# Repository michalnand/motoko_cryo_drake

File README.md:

# motoko cryo drake - line following robot

robot photos

# hardware

- main MCU stm32f722, cortex m7, 216MHz, FPU
- sensors MCU stm32g031, cortex m0, 64MHz
- BLDC motors, custom windings, custom silicone tires
- 3 phase drivers, 2 x MP6541, 8A drivers
- turbine - some random DC drone motor + 3D print
- line sensors : 10x phototransistor + white LED
- obstacle sensors : 4x IR photo diode
- power 2D LiPo, Dualsky 250mAh
- USB C, debug connectors, RGB leds

# robot PCB

4 layer pcb, designed in EasyEDA

# software 

inner loop, 2kHz : 
- FOC control for BLDC motors
- kalman filter state estimator

outer loop
- analytical MPC
- constrained path planner
- koopman operator non linear controller

# block diagram

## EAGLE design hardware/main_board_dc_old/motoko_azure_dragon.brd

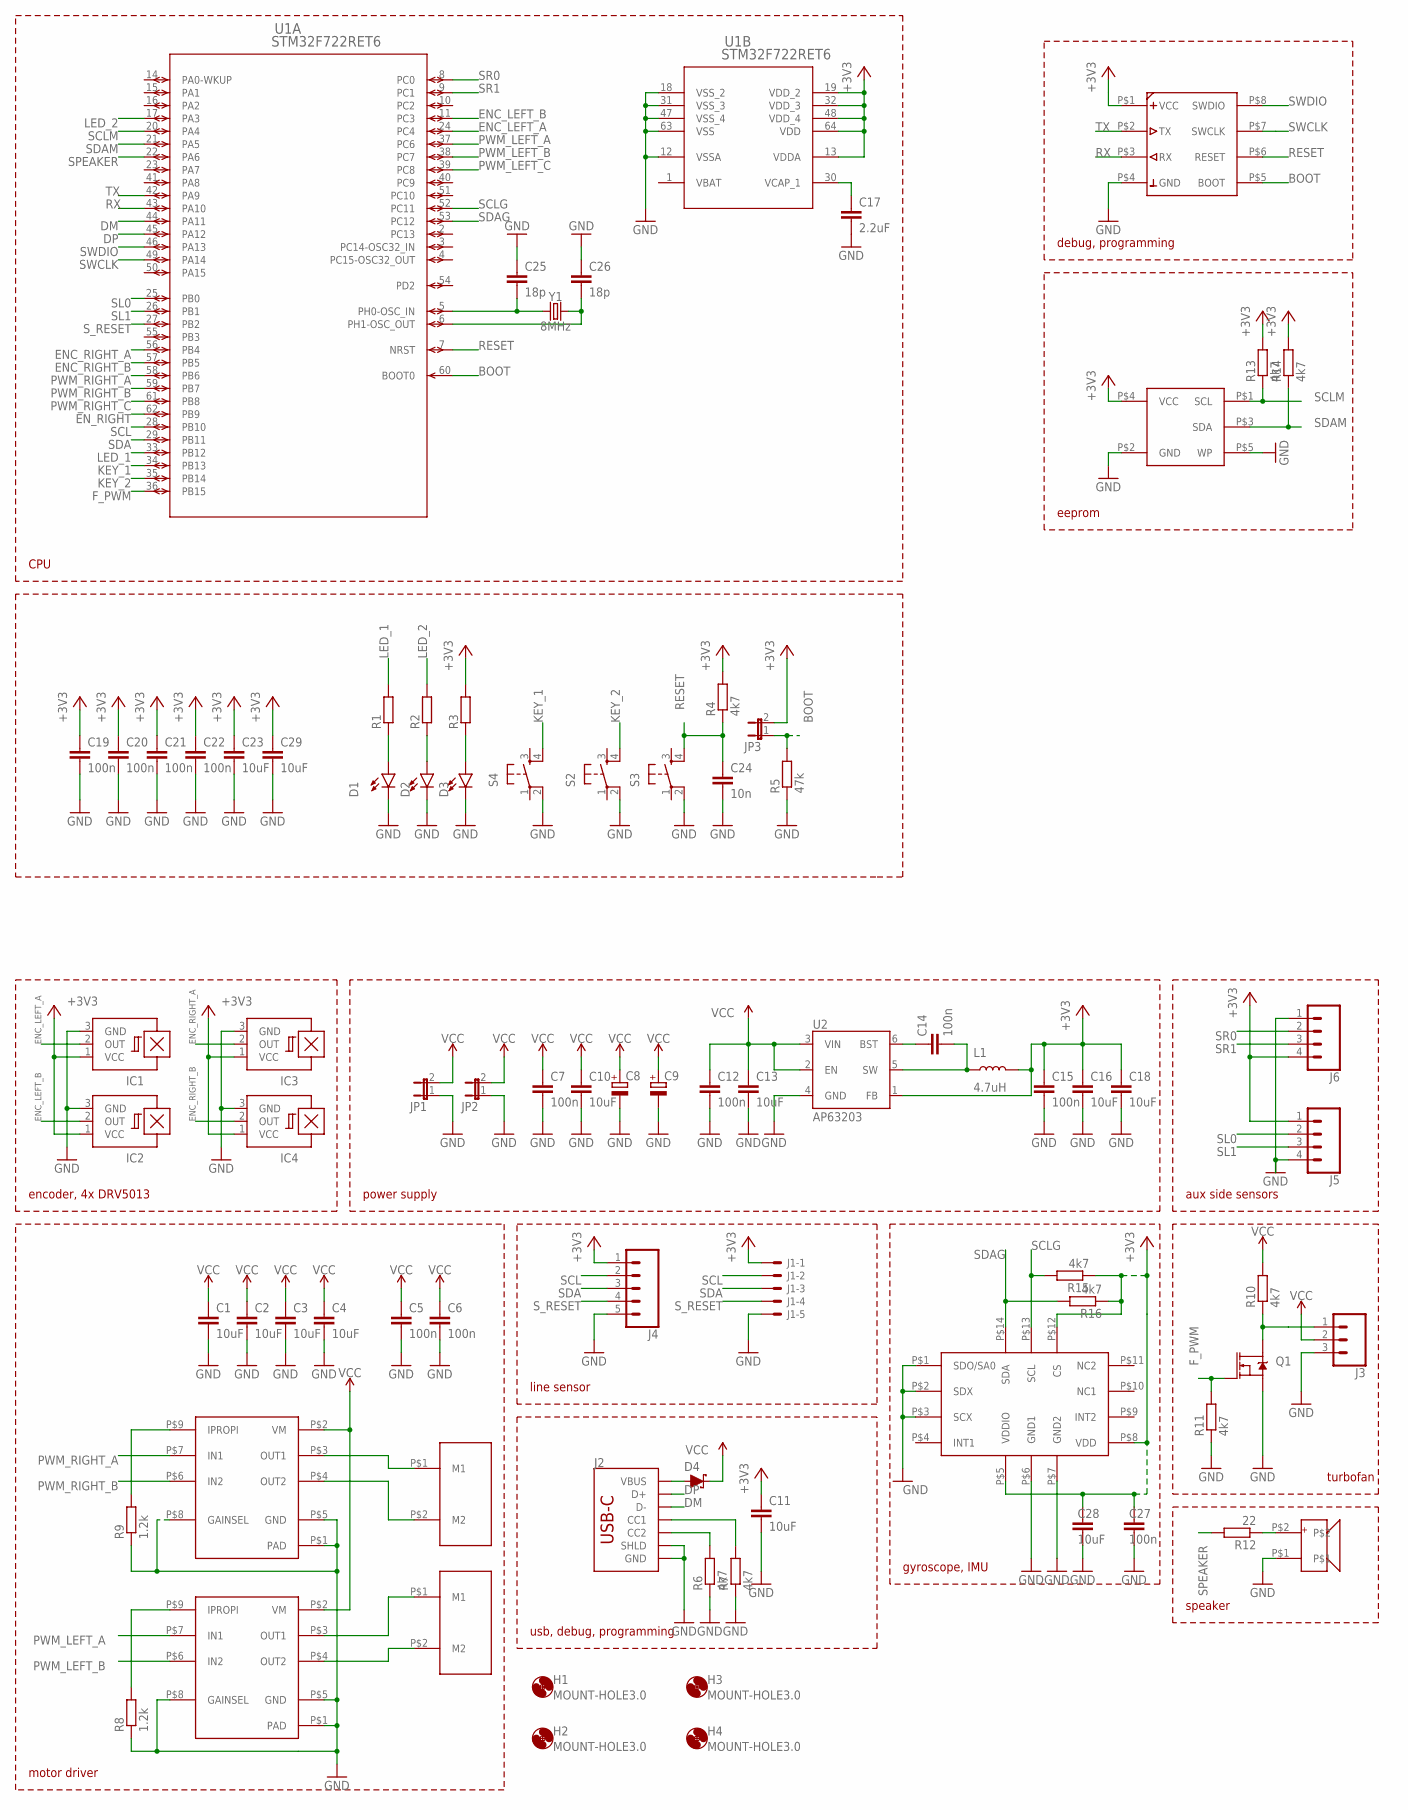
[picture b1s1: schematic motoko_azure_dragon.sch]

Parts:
C1, C2, C3, C4, C10, C11, C13, C16, C18, C23, C28, C29: 10uF; C0805
C5, C6, C7, C12, C14, C15, C19, C20, C21, C22, C27: 100n; C0805
C8, C9: CPOL-EUB/3528-21W; B/3528-21W
C17: 2.2uF; C0805
C24: 10n; C0805
C25, C26: 18p; C0805
D1, D2, D3: LED1206; LED-1206
D4: 3A/10V/280mV; SOD-323
H1, H2, H3, H4: MOUNT-HOLE3.0; 3,0
IC1, IC2, IC3, IC4: A1202LH; SOT23-W
J1: XF2L-0535-1
J2: USB_C_2-LAYER_PADS; USB-C-16P-2LAYER-PADS
J3: CONN_03LONGPADS; 1X03_LONGPADS
J4: CONN_051.27MM; 1X05_1.27MM
J5, J6: 1X04_SMD_STRAIGHT_COMBO; 1X04_SMD_VERTICAL_COMBO
JP1, JP2, JP3: JP1E; JP1
L1: 4.7uH; CR54
Q1: 5.8A/30V/35mΩ; SOT23-3
R1, R2, R3: R-EU_M0805; M0805
R4, R6, R7, R10, R11, R13, R14, R15, R16: 4k7; M0805
R5: 47k; M0805
R8, R9: 1.2k; M0805
R12: 22; M0805
S2, S3, S4: TAC_SWITCHSMD; TACTILE-SWITCH-SMD
U1: STM32F722RET6; LQFP64-10X10MM
U2: AP63203; SOT23-6
U$2, U$3: POLOLU_MICRO_METAL_GEAR_MOTOR
U$4, U$5: DRV8213; DSG8
U$6: 24LC24_SOT23; SOT23
U$7: DEBUG_CON; HEADER_4X2_1.27
U$8: LSM6DSM; LGA14L
U$9: SPEAKER_SMD_SMT0440
Y1: 8MHz; CRYSTAL-SMD-3.2X2.5MM

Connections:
+3V3: C11.1, C15.1, C16.1, C18.1, C19.1, C20.1, C21.1, C22.1, C23.1, C27.1, C28.1, C29.1, IC1.1 (VCC), IC2.1 (VCC), IC3.1 (VCC), IC4.1 (VCC), J1.1 (MSV), J4.1, J5.1, J6.4, JP3.2, L1.P$2 (2), R3.2, R4.2, R13.2, R14.2, R15.1, R16.1, U1.13 (VDDA), U1.19 (VDD_2), U1.32 (VDD_3), U1.48 (VDD_4), U1.64 (VDD), U2.1 (FB), U$6.P$4 (VCC), U$7.P$1 (VCC), U$8.P$5 (VDDIO), U$8.P$8 (VDD), U$8.P$12 (CS)
BOOT: JP3.1, R5.2, U1.60 (BOOT0), U$7.P$5 (BOOT)
DM: J2.A7 (D-), J2.B7 (D-), U1.44 (PA11)
DP: J2.A6 (D+), J2.B6 (D+), U1.45 (PA12)
ENC_LEFT_A: IC1.2 (OUT), U1.24 (PC4)
ENC_LEFT_B: IC2.2 (OUT), U1.11 (PC3)
ENC_RIGHT_A: IC3.2 (OUT), U1.56 (PB4)
ENC_RIGHT_B: IC4.2 (OUT), U1.57 (PB5)
EN_RIGHT: U1.62 (PB9)
F_PWM: Q1.1 (G), R11.2, U1.36 (PB15)
GND: C1.2, C2.2, C3.2, C4.2, C5.2, C6.2, C7.2, C8.-, C9.-, C10.2, C11.2, C12.2, C13.2, C15.2, C16.2, C17.2, C18.2, C19.2, C20.2, C21.2, C22.2, C23.2, C24.2, C25.1, C26.1, C27.2, C28.2, C29.2, D1.C, D2.C, D3.C, IC1.3 (GND), IC2.3 (GND), IC3.3 (GND), IC4.3 (GND), J1.5 (MS), J2.GND, J2.GND2 (GND), J2.SHLD1 (SHLD), J2.SHLD2 (SHLD), J2.SHLD3 (SHLD), J2.SHLD4 (SHLD), J3.3, J4.5, J5.4, J6.1, JP1.1, JP2.1, Q1.2 (S), R5.1, R6.1, R7.1, R8.1, R9.1, R11.1, S2.2, S3.2, S4.2, U1.12 (VSSA), U1.18 (VSS_2), U1.31 (VSS_3), U1.47 (VSS_4), U1.63 (VSS), U2.4 (GND), U$4.P$1 (PAD), U$4.P$5 (GND), U$4.P$8 (GAINSEL), U$5.P$1 (PAD), U$5.P$5 (GND), U$5.P$8 (GAINSEL), U$6.P$2 (GND), U$6.P$5 (WP), U$7.P$4 (GND), U$8.P$1 (SDO/SA0), U$8.P$2 (SDX), U$8.P$3 (SCX), U$8.P$6 (GND1), U$8.P$7 (GND2), U$9.P$1
KEY_1: S4.4, U1.34 (PB13)
KEY_2: S2.4, U1.35 (PB14)
LED_1: R1.2, U1.33 (PB12)
LED_2: R2.2, U1.17 (PA3)
unnamed: U$3.P$2 (M2), U$5.P$4 (OUT2)
unnamed: U$3.P$1 (M1), U$5.P$3 (OUT1)
unnamed: U$2.P$2 (M2), U$4.P$4 (OUT2)
unnamed: U$2.P$1 (M1), U$4.P$3 (OUT1)
unnamed: C14.2, L1.P$1 (1), U2.5 (SW)
unnamed: C14.1, U2.6 (BST)
unnamed: D1.A, R1.1
unnamed: D2.A, R2.1
unnamed: D3.A, R3.1
unnamed: J2.B5 (CC2), R6.2
unnamed: J2.A5 (CC1), R7.2
unnamed: C17.1, U1.30 (VCAP_1)
unnamed: C25.2, U1.5 (PH0-OSC_IN), Y1.1
unnamed: C26.2, U1.6 (PH1-OSC_OUT), Y1.3 (2)
unnamed: R8.2, U$5.P$9 (IPROPI)
unnamed: R9.2, U$4.P$9 (IPROPI)
unnamed: D4.A, J2.VBUS1 (VBUS), J2.VBUS2 (VBUS)
unnamed: J3.1, Q1.3 (D), R10.1
unnamed: R12.1, U$9.P$2
PWM_LEFT_A: U1.37 (PC6), U$5.P$7 (IN1)
PWM_LEFT_B: U1.38 (PC7), U$5.P$6 (IN2)
PWM_LEFT_C: U1.39 (PC8)
PWM_RIGHT_A: U1.58 (PB6), U$4.P$7 (IN1)
PWM_RIGHT_B: U1.59 (PB7), U$4.P$6 (IN2)
PWM_RIGHT_C: U1.61 (PB8)
RESET: C24.1, R4.1, S3.4, U1.7 (NRST), U$7.P$6 (RESET)
RX: U1.43 (PA10), U$7.P$3 (RX)
SCL: J1.2 (MS), J4.2, U1.28 (PB10)
SCLG: R15.2, U1.52 (PC11), U$8.P$13 (SCL)
SCLM: R13.1, U1.20 (PA4), U$6.P$1 (SCL)
SDA: J1.3 (MS), J4.3, U1.29 (PB11)
SDAG: R16.2, U1.53 (PC12), U$8.P$14 (SDA)
SDAM: R14.1, U1.21 (PA5), U$6.P$3 (SDA)
SL0: J5.2, U1.25 (PB0)
SL1: J5.3, U1.26 (PB1)
SPEAKER: R12.2, U1.22 (PA6)
SR0: J6.2, U1.8 (PC0)
SR1: J6.3, U1.9 (PC1)
SWCLK: U1.49 (PA14), U$7.P$7 (SWCLK)
SWDIO: U1.46 (PA13), U$7.P$8 (SWDIO)
S_RESET: J1.4 (MS), J4.4, U1.27 (PB2)
TX: U1.42 (PA9), U$7.P$2 (TX)
VBAT: U1.1 (VBAT)
VCC: C1.1, C2.1, C3.1, C4.1, C5.1, C6.1, C7.1, C8.+, C9.+, C10.1, C12.1, C13.1, D4.C, J3.2, JP1.2, JP2.2, R10.2, U2.2 (EN), U2.3 (VIN), U$4.P$2 (VM), U$5.P$2 (VM)

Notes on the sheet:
encoder, 4x DRV5013
motor driver
power supply
line sensor
aux side sensors
usb, debug, programming
turbofan
gyroscope, IMU
speaker
debug, programming
eeprom
CPU

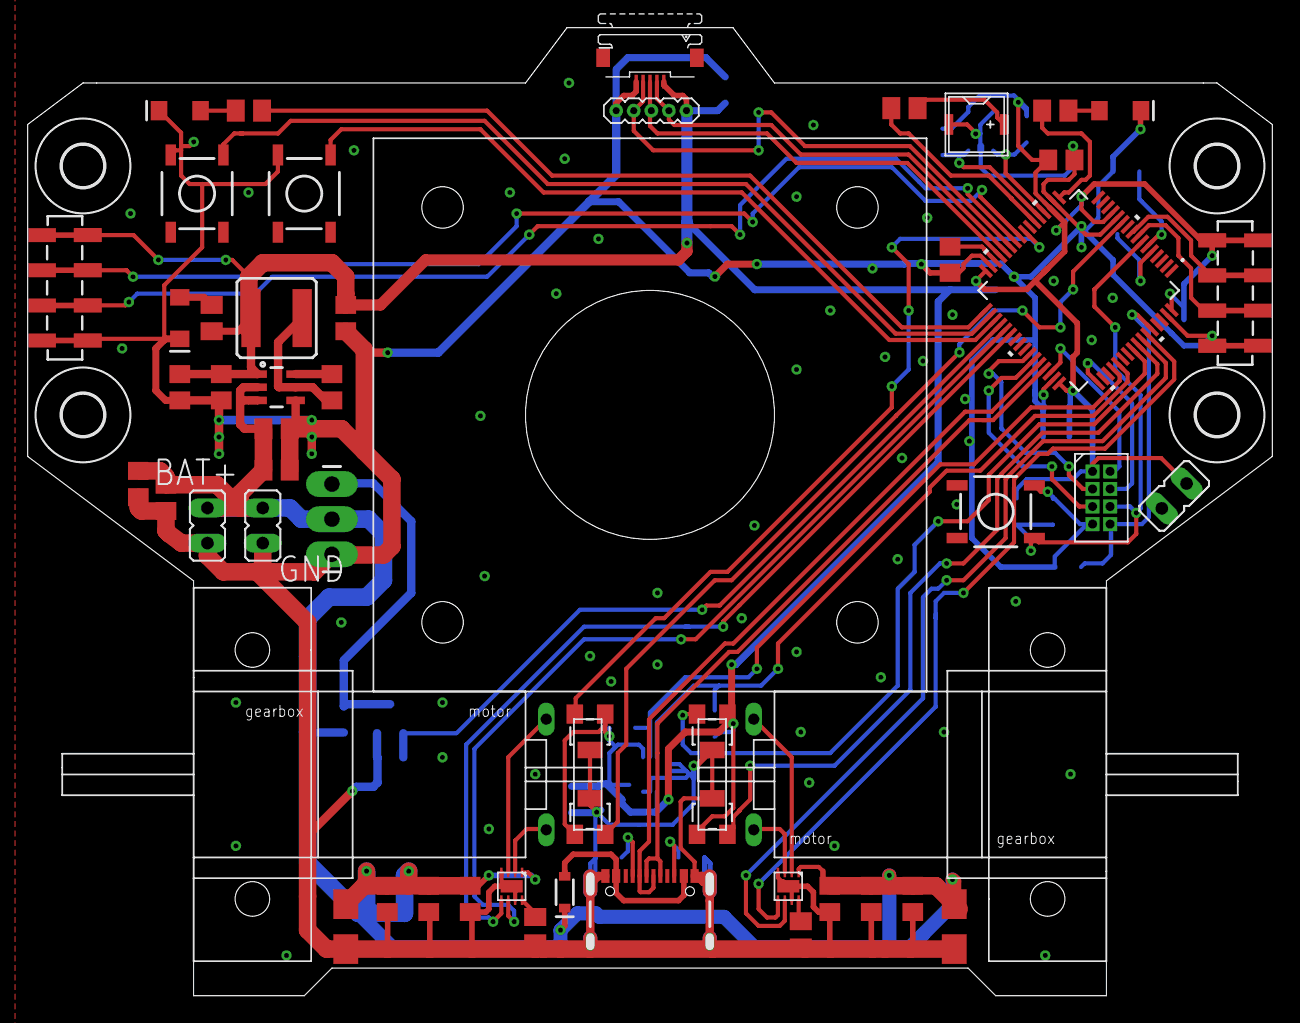
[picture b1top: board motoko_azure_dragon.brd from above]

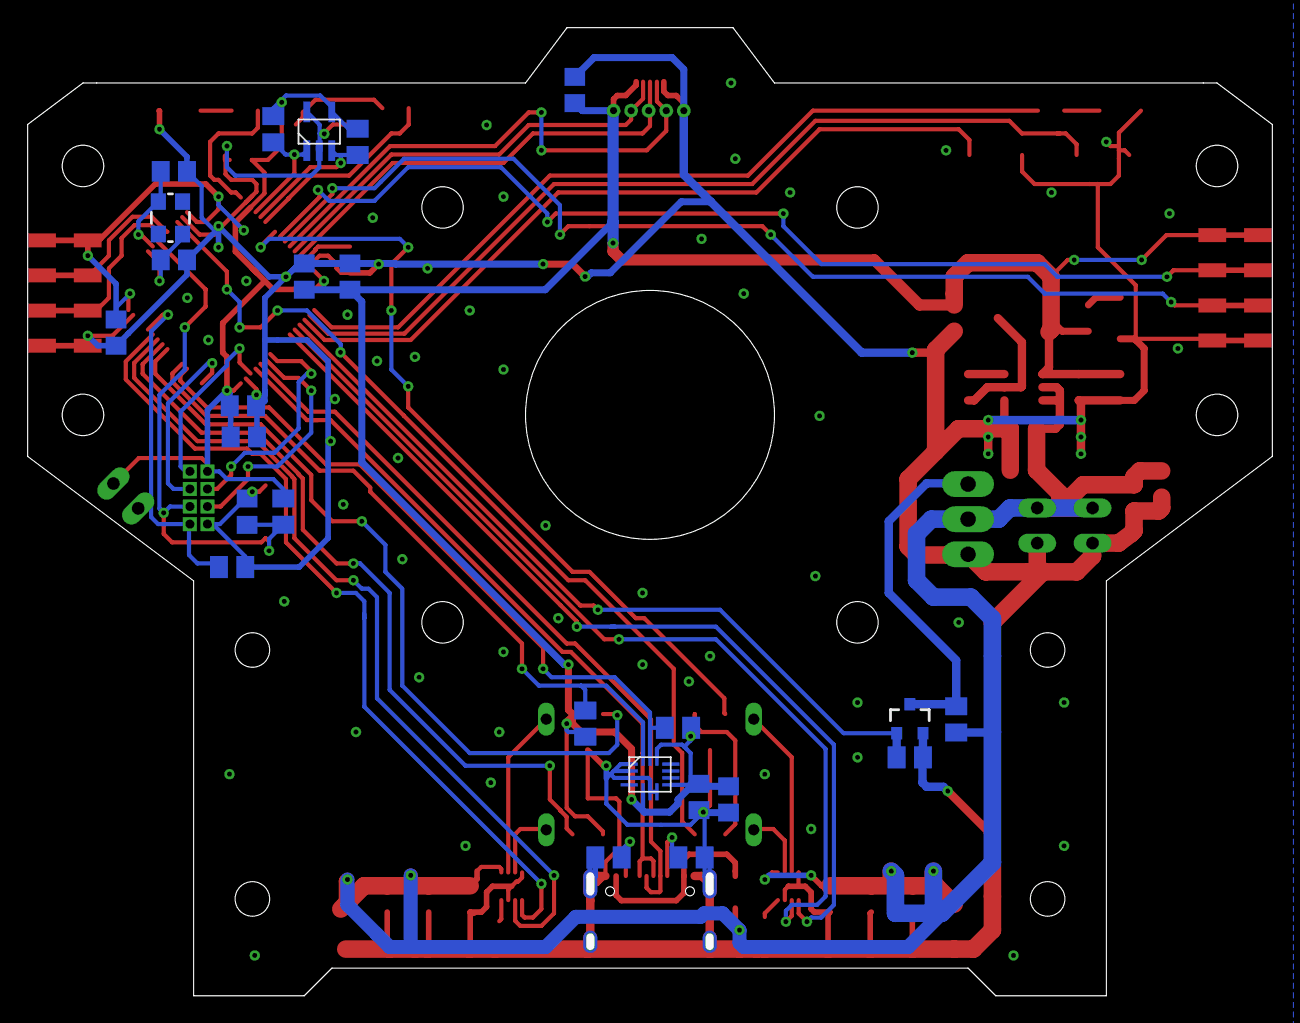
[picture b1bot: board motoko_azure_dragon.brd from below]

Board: 2 copper layers, 89.4 x 69.4 mm, 83 parts (25 on the bottom side), 55 nets.

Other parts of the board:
U$1: DUCTED_FAN_40MM

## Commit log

2026-01-31 initial
2026-03-05 turbine test
2026-03-09 sensors
2026-03-10 sensors tested + driver, FOC for motors + encoders tests, open loop control
2026-03-11 motor identification
2026-03-11 motor controller + state estimator
2026-03-12 system identification
2026-03-14 input shaper
2026-03-17 model identification, controller
2026-03-19 identification fix + lqr fix
2026-03-19 mpc simulation
2026-03-20 mpc controller
2026-03-21 mpc, shapers
2026-03-22 mpc control
2026-03-23 fixed turn
2026-03-23 code cleaned
2026-03-24 trajectory planner - not tested
2026-03-27 path planner first tests
2026-03-31 first line following integration
2026-04-06 first line following
2026-04-07 koopman controller - not tested yet
2026-04-08 ide jak pila
2026-04-11 broken line, params tunned
2026-04-12 proximity sensors calibration
2026-04-13 obstacle avoid, not tested
2026-04-19 something is working
2026-04-25 istrobot day

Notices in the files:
parts and their libraries:
SparkFun-Connectors: Licensing: Creative Commons ShareAlike 4.0 International - https://creativecommons.org/licenses/by-sa/4.0
COPYRIGHT: Copyright (C) 2024 Ultra Librarian. All rights reserved.
